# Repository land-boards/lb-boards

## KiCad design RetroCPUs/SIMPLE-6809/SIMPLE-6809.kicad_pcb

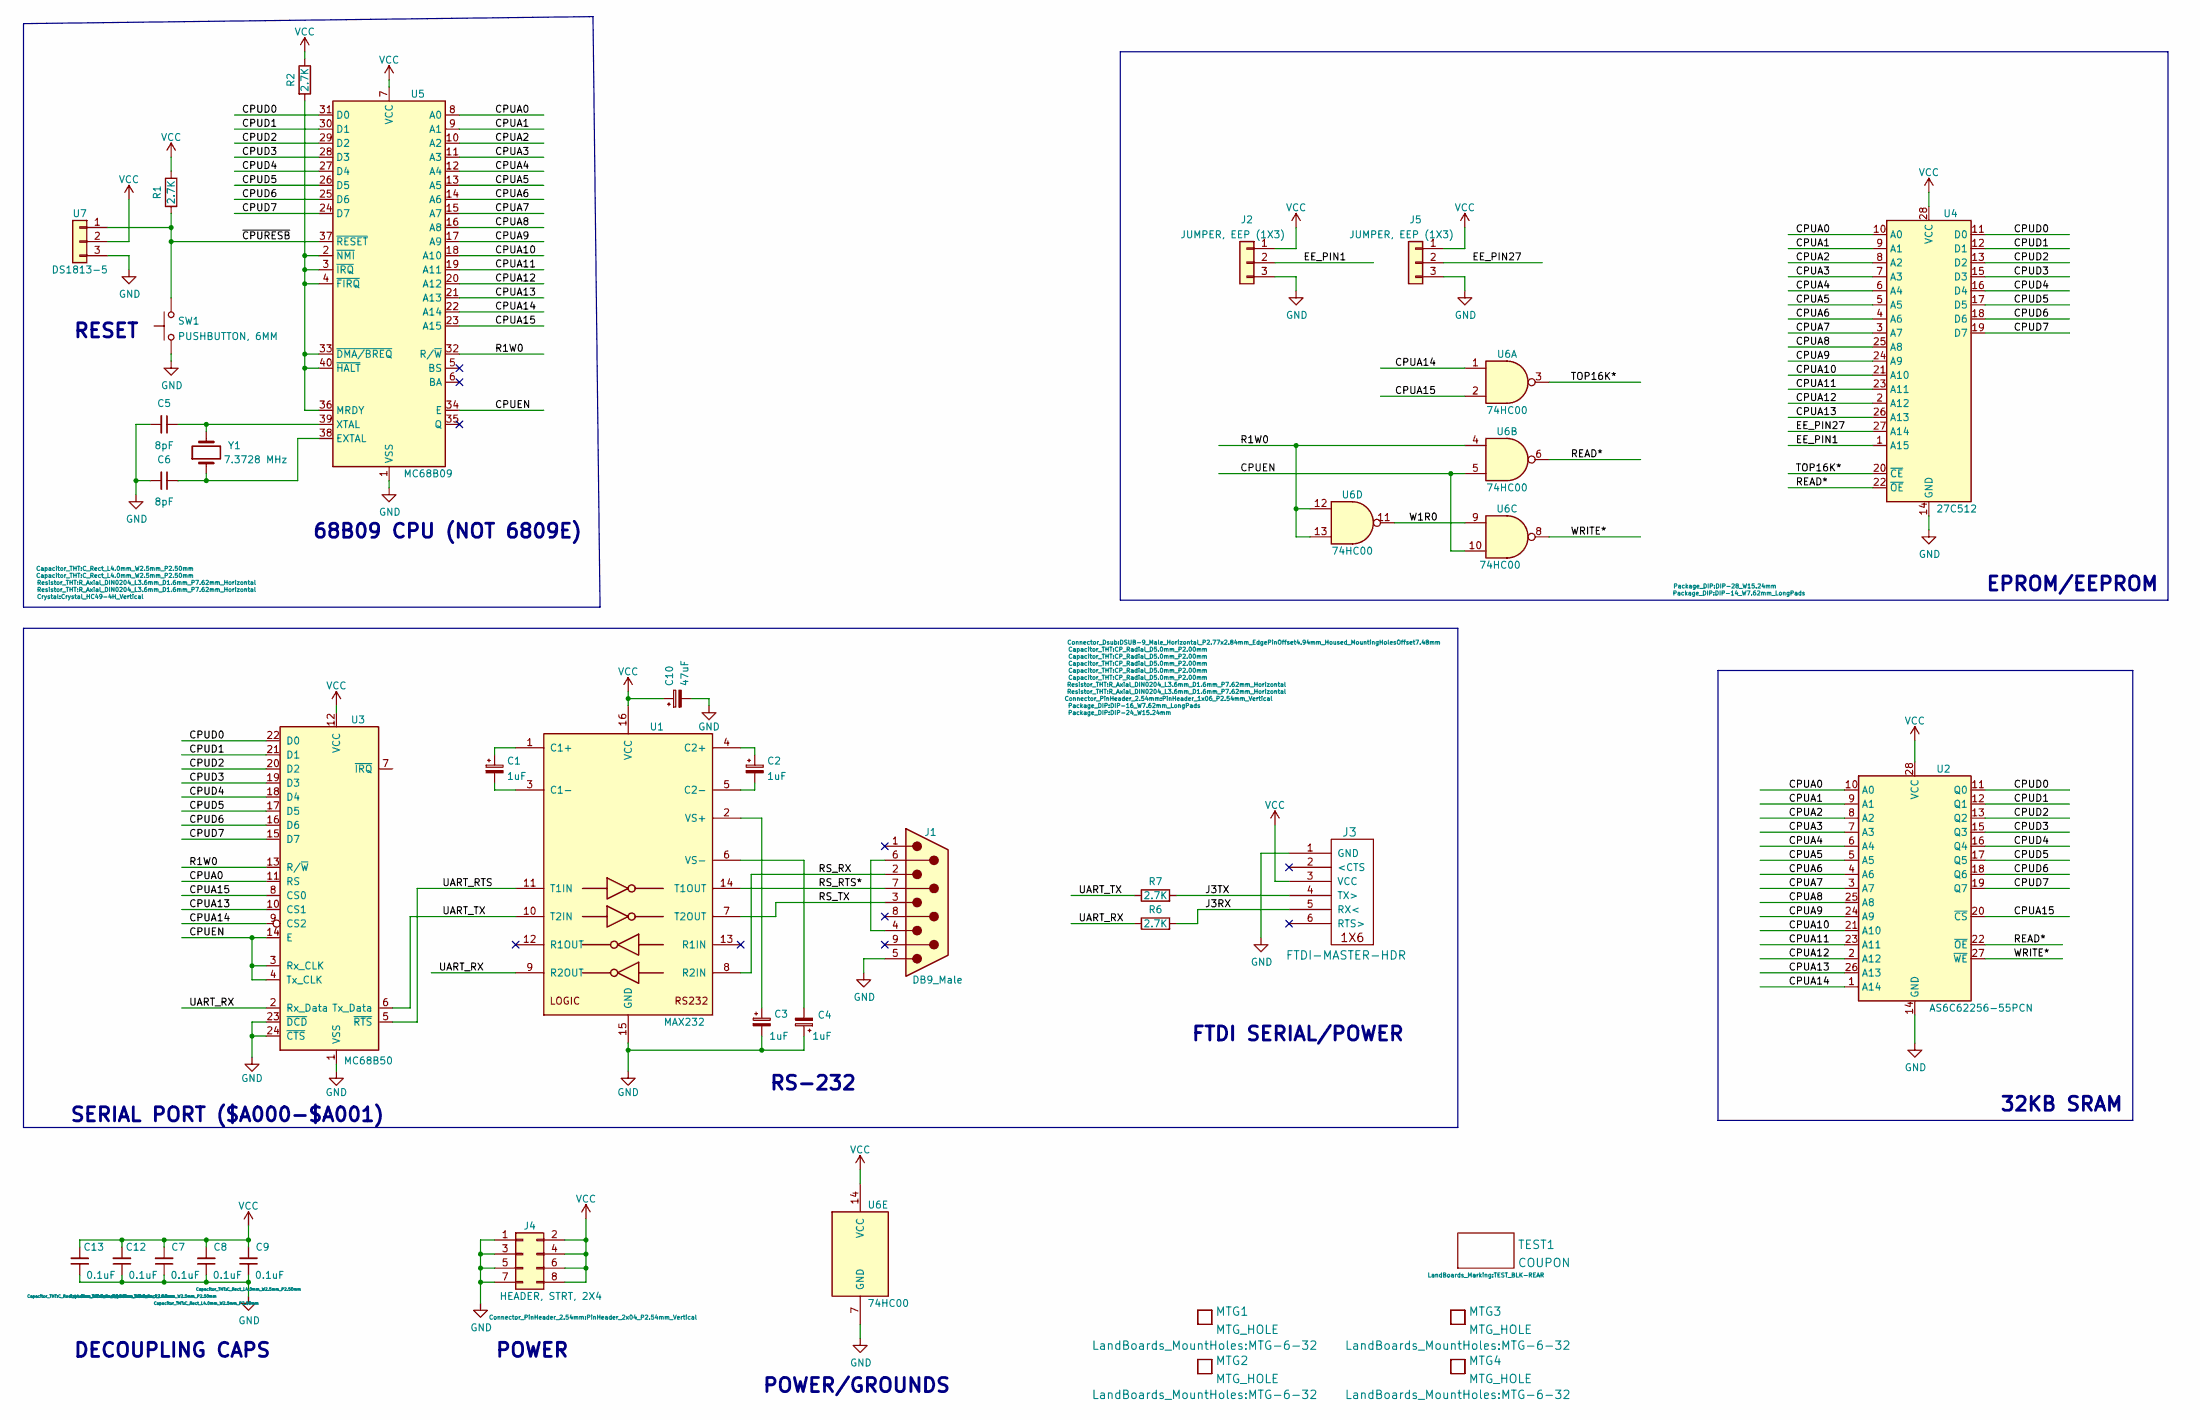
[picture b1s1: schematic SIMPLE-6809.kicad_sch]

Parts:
C1, C2, C3, C4: 1uF; CP_Radial_D5.0mm_P2.00mm
C5, C6: 8pF; C_Rect_L4.0mm_W2.5mm_P2.50mm
C7, C8, C9, C12, C13: 0.1uF; C_Rect_L4.0mm_W2.5mm_P2.50mm
C10: 47uF; CP_Radial_D5.0mm_P2.00mm
J1: DB9_Male; DSUB-9_Male_Horizontal_P2.77x2.84mm_EdgePinOffset4.94mm_Hou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
J2, J5: JUMPER, EEP (1X3); PinHeader_1x03_P2.54mm_Vertical
J3: FTDI-MASTER-HDR; PinHeader_1x06_P2.54mm_Vertical
J4: HEADER, STRT, 2X4; PinHeader_2x04_P2.54mm_Vertical
MTG1, MTG2, MTG3, MTG4: MTG_HOLE; MTG-6-32
R1, R2, R6, R7: 2.7K; R_Axial_DIN0204_L3.6mm_D1.6mm_P7.62mm_Horizontal
SW1: PUSHBUTTON, 6MM; SW_PUSH_6mm_H8.5mm
TEST1: COUPON; TEST_BLK-REAR
U1: MAX232; DIP-16_W7.62mm_LongPads
U2: AS6C62256-55PCN; DIP-28_W15.24mm
U3: MC68B50; DIP-24_W15.24mm
U4: 27C512; DIP-28_W15.24mm
U5: MC68B09; DIP-40_W15.24mm
U6: 74HC00; DIP-14_W7.62mm_LongPads
U7: DS1813-5; TO-92
Y1: 7.3728 MHz; Crystal_HC49-4H_Vertical

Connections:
/CPUA0: U2.10 (A0), U3.11 (RS), U4.10 (A0), U5.8 (A0)
/CPUA1: U2.9 (A1), U4.9 (A1), U5.9 (A1)
/CPUA2: U2.8 (A2), U4.8 (A2), U5.10 (A2)
/CPUA3: U2.7 (A3), U4.7 (A3), U5.11 (A3)
/CPUA4: U2.6 (A4), U4.6 (A4), U5.12 (A4)
/CPUA5: U2.5 (A5), U4.5 (A5), U5.13 (A5)
/CPUA6: U2.4 (A6), U4.4 (A6), U5.14 (A6)
/CPUA7: U2.3 (A7), U4.3 (A7), U5.15 (A7)
/CPUA8: U2.25 (A8), U4.25 (A8), U5.16 (A8)
/CPUA9: U2.24 (A9), U4.24 (A9), U5.17 (A9)
/CPUA10: U2.21 (A10), U4.21 (A10), U5.18 (A10)
/CPUA11: U2.23 (A11), U4.23 (A11), U5.19 (A11)
/CPUA12: U2.2 (A12), U4.2 (A12), U5.20 (A12)
/CPUA13: U2.26 (A13), U3.10 (CS1), U4.26 (A13), U5.21 (A13)
/CPUA14: U2.1 (A14), U3.9 (CS2), U5.22 (A14), U6.1
/CPUA15: U2.20 (~CS), U3.8 (CS0), U5.23 (A15), U6.2
/CPUD0: U2.11 (Q0), U3.22 (D0), U4.11 (D0), U5.31 (D0)
/CPUD1: U2.12 (Q1), U3.21 (D1), U4.12 (D1), U5.30 (D1)
/CPUD2: U2.13 (Q2), U3.20 (D2), U4.13 (D2), U5.29 (D2)
/CPUD3: U2.15 (Q3), U3.19 (D3), U4.15 (D3), U5.28 (D3)
/CPUD4: U2.16 (Q4), U3.18 (D4), U4.16 (D4), U5.27 (D4)
/CPUD5: U2.17 (Q5), U3.17 (D5), U4.17 (D5), U5.26 (D5)
/CPUD6: U2.18 (Q6), U3.16 (D6), U4.18 (D6), U5.25 (D6)
/CPUD7: U2.19 (Q7), U3.15 (D7), U4.19 (D7), U5.24 (D7)
/CPUEN: U3.3 (Rx_CLK), U3.4 (Tx_CLK), U3.14 (E), U5.34 (E), U6.5, U6.10
/EE_PIN1: J2.2, U4.1 (A15)
/EE_PIN27: J5.2, U4.27 (A14)
/J3RX: J3.5 (RX<), R6.2
/J3TX: J3.4 (TX>), R7.2
/R1W0: U3.13 (R/~W), U5.32 (R/~W), U6.4, U6.12, U6.13
/READ*: U2.22 (~OE), U4.22 (~OE), U6.6
/RS_RTS*: J1.7, U1.14 (T1OUT)
/RS_RX: J1.2, U1.8 (R2IN)
/RS_TX: J1.3, U1.7 (T2OUT)
/TOP16K*: U4.20 (~CE), U6.3
/UART_RTS: U1.11 (T1IN), U3.5 (~RTS)
/UART_RX: R6.1, U1.9 (R2OUT), U3.2 (Rx_Data)
/UART_TX: R7.1, U1.10 (T2IN), U3.6 (Tx_Data)
/W1R0: U6.9, U6.11
/WRITE*: U2.27 (~WE), U6.8
/~CPURESB: R1.2, SW1.2, U5.37 (~RESET), U7.1
GND: C3.2, C4.1, C5.2, C6.2, C7.1, C8.1, C9.1, C10.2, C12.1, C13.1, J1.5, J2.3, J3.1 (GND), J4.1, J4.3, J4.5, J4.7, J5.3, SW1.1, U1.15 (GND), U2.14 (GND), U3.1 (VSS), U3.23 (~DCD), U3.24 (~CTS), U4.14 (GND), U5.1 (VSS), U6.7 (GND), U7.3
unnamed: J1.4, J1.6
unnamed: C1.1, U1.1 (C1+)
unnamed: C1.2, U1.3 (C1-)
unnamed: C2.1, U1.4 (C2+)
unnamed: C2.2, U1.5 (C2-)
unnamed: C3.1, U1.2 (VS+)
unnamed: C4.2, U1.6 (VS-)
unnamed: C6.1, U5.38 (EXTAL), Y1.1
unnamed: R2.2, U5.2 (~NMI), U5.3 (~IRQ), U5.4 (~FIRQ), U5.33 (~DMA/BREQ), U5.36 (MRDY), U5.40 (~HALT)
unnamed: C5.1, U5.39 (XTAL), Y1.2
VCC: C7.2, C8.2, C9.2, C10.1, C12.2, C13.2, J2.1, J3.3 (VCC), J4.2, J4.4, J4.6, J4.8, J5.1, R1.1, R2.1, U1.16 (VCC), U2.28 (VCC), U3.12 (VCC), U4.28 (VCC), U5.7 (VCC), U6.14 (VCC), U7.2

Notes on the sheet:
POWER
RESET
32KB SRAM
DECOUPLING CAPS
FTDI SERIAL/POWER
SERIAL PORT ($A000-$A001)
POWER/GROUNDS
EPROM/EEPROM
68B09 CPU (NOT 6809E)
RS-232

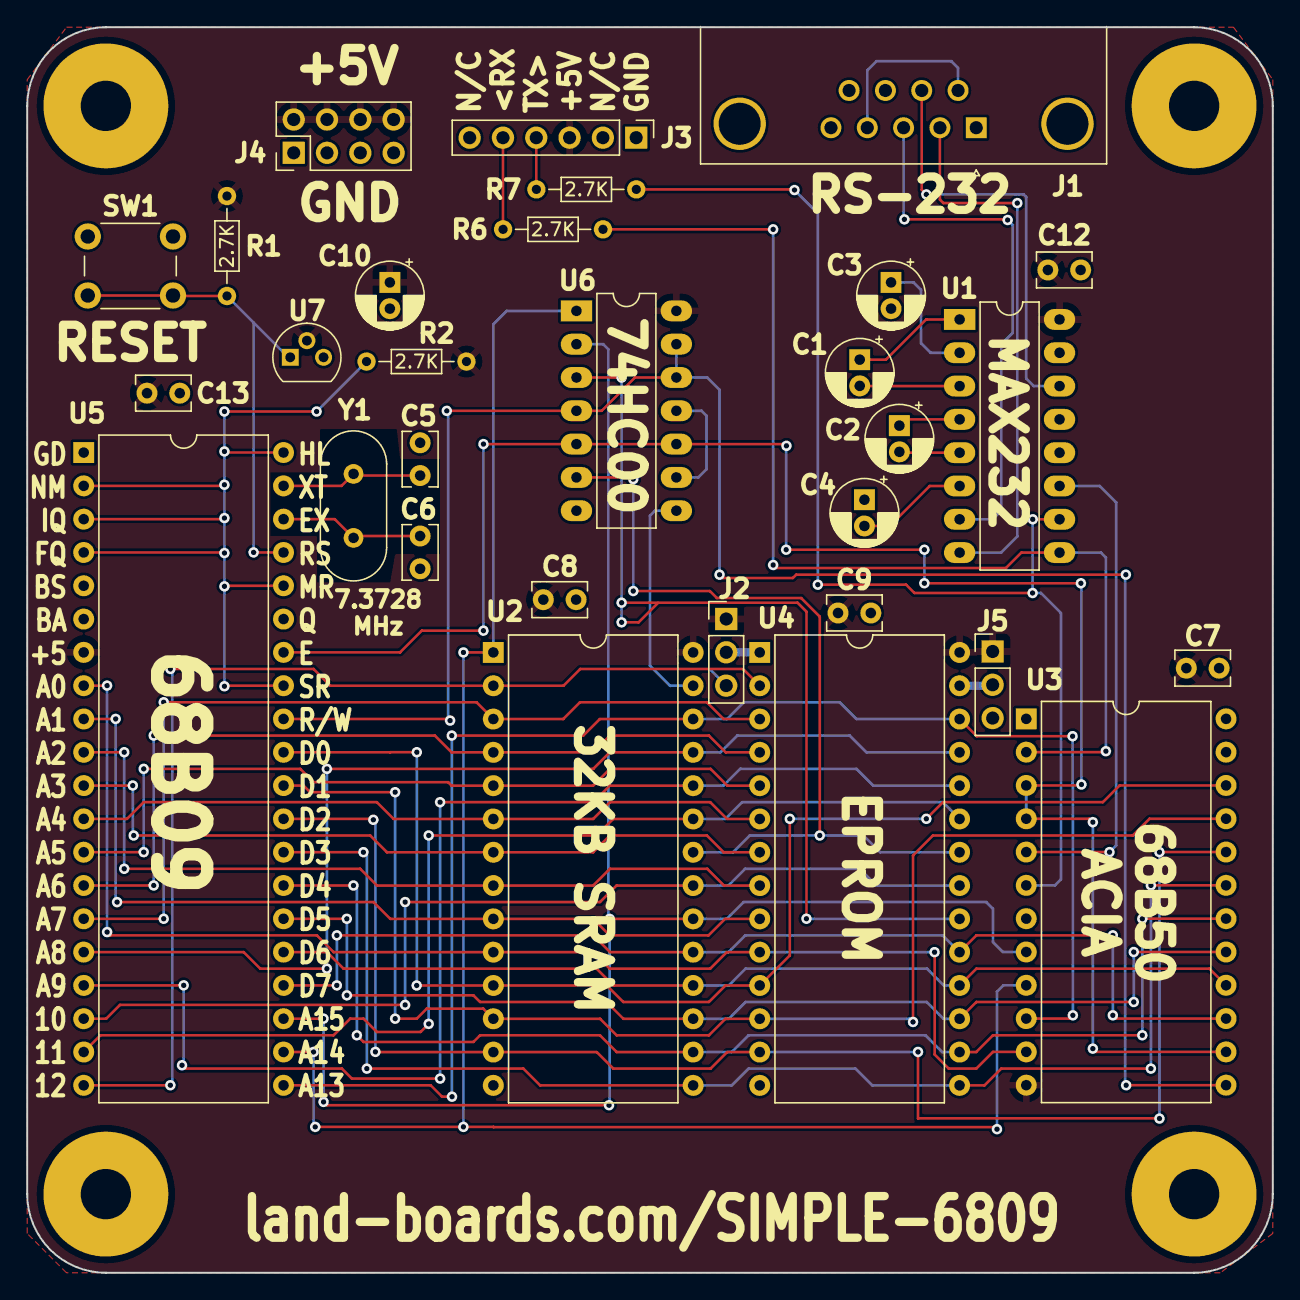
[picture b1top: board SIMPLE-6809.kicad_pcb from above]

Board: 2 copper layers, 95.0 x 95.0 mm, 35 parts (0 on the bottom side), 53 nets.

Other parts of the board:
TEST: COUPON; TEST_BLK-REAR

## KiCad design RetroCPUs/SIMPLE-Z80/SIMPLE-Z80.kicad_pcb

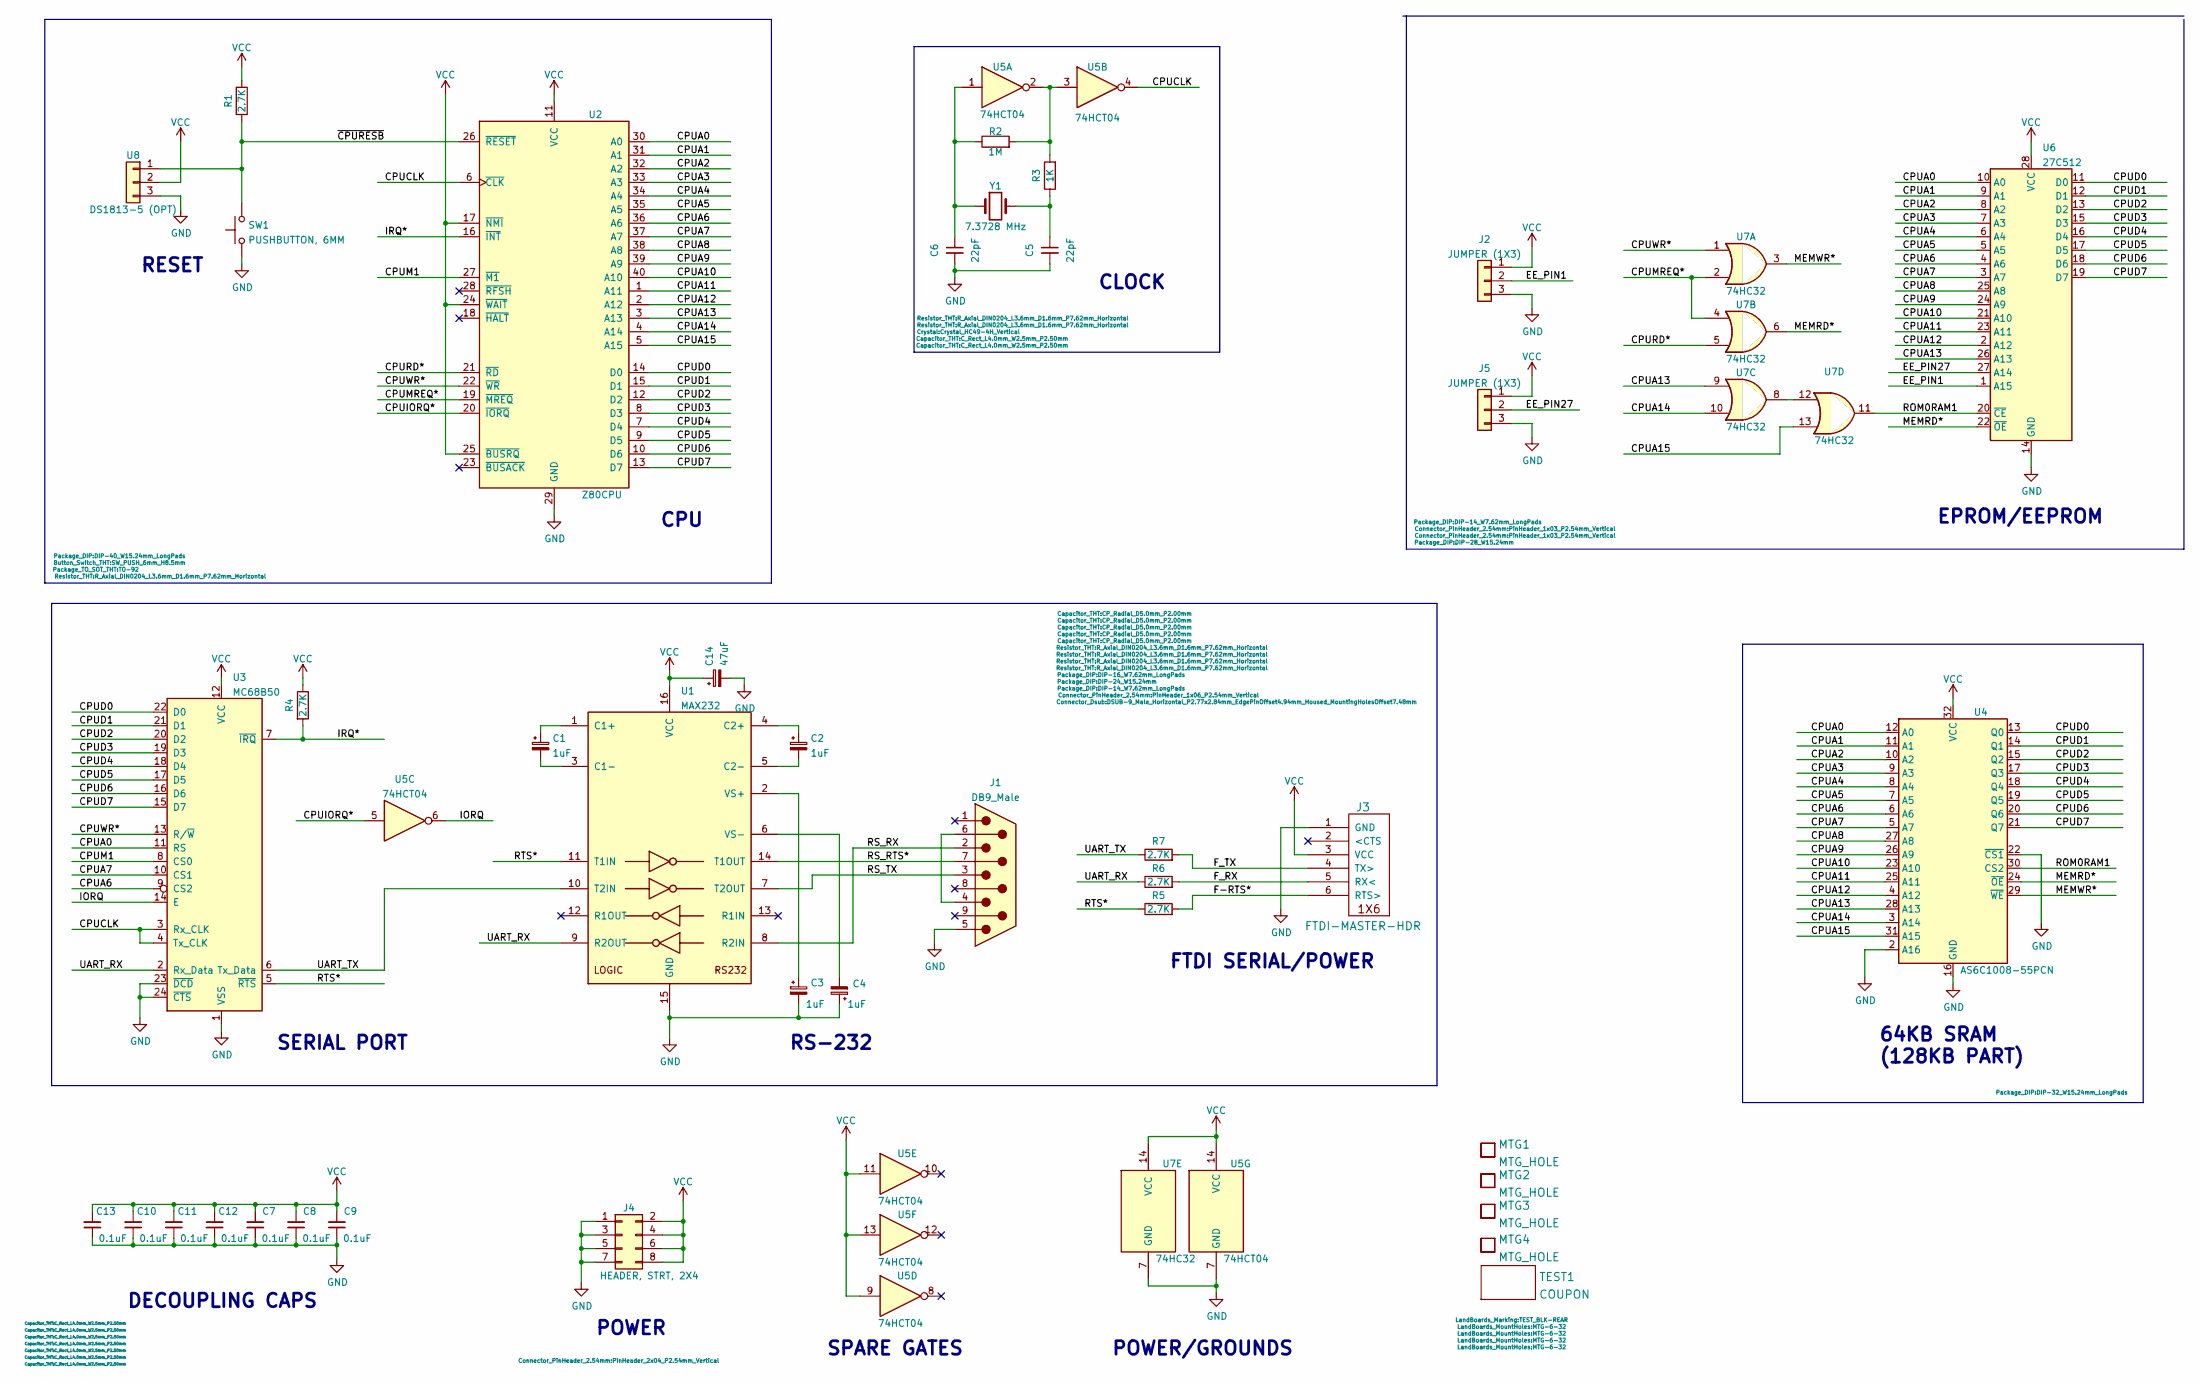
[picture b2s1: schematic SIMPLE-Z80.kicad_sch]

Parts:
C1, C2, C3, C4: 1uF; CP_Radial_D5.0mm_P2.00mm
C5, C6: 22pF; C_Rect_L4.0mm_W2.5mm_P2.50mm
C7, C8, C9, C10, C11, C12, C13: 0.1uF; C_Rect_L4.0mm_W2.5mm_P2.50mm
C14: 47uF; CP_Radial_D5.0mm_P2.00mm
J1: DB9_Male; DSUB-9_Male_Horizontal_P2.77x2.84mm_EdgePinOffset4.94mm_Hou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
J2, J5: JUMPER (1X3); PinHeader_1x03_P2.54mm_Vertical
J3: FTDI-MASTER-HDR; PinHeader_1x06_P2.54mm_Vertical
J4: HEADER, STRT, 2X4; PinHeader_2x04_P2.54mm_Vertical
MTG1, MTG2, MTG3, MTG4: MTG_HOLE; MTG-6-32
R1, R4, R5, R6, R7: 2.7K; R_Axial_DIN0204_L3.6mm_D1.6mm_P7.62mm_Horizontal
R2: 1M; R_Axial_DIN0204_L3.6mm_D1.6mm_P7.62mm_Horizontal
R3: 1K; R_Axial_DIN0204_L3.6mm_D1.6mm_P7.62mm_Horizontal
SW1: PUSHBUTTON, 6MM; SW_PUSH_6mm_H8.5mm
TEST1: COUPON; TEST_BLK-REAR
U1: MAX232; DIP-16_W7.62mm_LongPads
U2: Z80CPU; DIP-40_W15.24mm_LongPads
U3: MC68B50; DIP-24_W15.24mm
U4: AS6C1008-55PCN; DIP-32_W15.24mm_LongPads
U5: 74HCT04; DIP-14_W7.62mm_LongPads
U6: 27C512; DIP-28_W15.24mm
U7: 74HC32; DIP-14_W7.62mm_LongPads
U8: DS1813-5 (OPT); TO-92
Y1: 7.3728 MHz; Crystal_HC49-4H_Vertical

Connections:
/CPUA0: U2.30 (A0), U3.11 (RS), U4.12 (A0), U6.10 (A0)
/CPUA1: U2.31 (A1), U4.11 (A1), U6.9 (A1)
/CPUA2: U2.32 (A2), U4.10 (A2), U6.8 (A2)
/CPUA3: U2.33 (A3), U4.9 (A3), U6.7 (A3)
/CPUA4: U2.34 (A4), U4.8 (A4), U6.6 (A4)
/CPUA5: U2.35 (A5), U4.7 (A5), U6.5 (A5)
/CPUA6: U2.36 (A6), U3.9 (CS2), U4.6 (A6), U6.4 (A6)
/CPUA7: U2.37 (A7), U3.10 (CS1), U4.5 (A7), U6.3 (A7)
/CPUA8: U2.38 (A8), U4.27 (A8), U6.25 (A8)
/CPUA9: U2.39 (A9), U4.26 (A9), U6.24 (A9)
/CPUA10: U2.40 (A10), U4.23 (A10), U6.21 (A10)
/CPUA11: U2.1 (A11), U4.25 (A11), U6.23 (A11)
/CPUA12: U2.2 (A12), U4.4 (A12), U6.2 (A12)
/CPUA13: U2.3 (A13), U4.28 (A13), U6.26 (A13), U7.9
/CPUA14: U2.4 (A14), U4.3 (A14), U7.10
/CPUA15: U2.5 (A15), U4.31 (A15), U7.13
/CPUCLK: U2.6 (~CLK), U3.3 (Rx_CLK), U3.4 (Tx_CLK), U5.4
/CPUD0: U2.14 (D0), U3.22 (D0), U4.13 (Q0), U6.11 (D0)
/CPUD1: U2.15 (D1), U3.21 (D1), U4.14 (Q1), U6.12 (D1)
/CPUD2: U2.12 (D2), U3.20 (D2), U4.15 (Q2), U6.13 (D2)
/CPUD3: U2.8 (D3), U3.19 (D3), U4.17 (Q3), U6.15 (D3)
/CPUD4: U2.7 (D4), U3.18 (D4), U4.18 (Q4), U6.16 (D4)
/CPUD5: U2.9 (D5), U3.17 (D5), U4.19 (Q5), U6.17 (D5)
/CPUD6: U2.10 (D6), U3.16 (D6), U4.20 (Q6), U6.18 (D6)
/CPUD7: U2.13 (D7), U3.15 (D7), U4.21 (Q7), U6.19 (D7)
/CPUIORQ*: U2.20 (~IORQ), U5.5
/CPUM1: U2.27 (~M1), U3.8 (CS0)
/CPUMREQ*: U2.19 (~MREQ), U7.2, U7.4
/CPURD*: U2.21 (~RD), U7.5
/CPUWR*: U2.22 (~WR), U3.13 (R/~W), U7.1
/EE_PIN1: J2.2, U6.1 (A15)
/EE_PIN27: J5.2, U6.27 (A14)
/F-RTS*: J3.6 (CTS>), R5.2
/F_RX: J3.5 (TX<), R6.2
/F_TX: J3.4 (RX>), R7.2
/IORQ: U3.14 (E), U5.6
/IRQ*: R4.2, U2.16 (~INT), U3.7 (~IRQ)
/MEMRD*: U4.24 (~OE), U6.22 (~OE), U7.6
/MEMWR*: U4.29 (~WE), U7.3
/ROM0RAM1: U4.30 (CS2), U6.20 (~CE), U7.11
/RS_RTS*: J1.7, U1.14 (T1OUT)
/RS_RX: J1.2, U1.8 (R2IN)
/RS_TX: J1.3, U1.7 (T2OUT)
/RTS*: R5.1, U1.11 (T1IN), U3.5 (~RTS)
/UART_RX: R6.1, U1.9 (R2OUT), U3.2 (Rx_Data)
/UART_TX: R7.1, U1.10 (T2IN), U3.6 (Tx_Data)
/~CPURESB: R1.2, SW1.2, U2.26 (~RESET), U8.1
GND: C3.2, C4.1, C5.2, C6.2, C7.1, C8.1, C9.1, C10.1, C11.1, C12.1, C13.1, C14.2, J1.5, J2.3, J3.1 (GND), J4.1, J4.3, J4.5, J4.7, J5.3, SW1.1, U1.15 (GND), U2.29 (GND), U3.1 (VSS), U3.23 (~DCD), U3.24 (~CTS), U4.2 (A16), U4.16 (GND), U4.22 (~CS1), U5.7 (GND), U6.14 (GND), U7.7 (GND), U8.3
unnamed: C5.1, R3.1, Y1.2
unnamed: C6.1, R2.1, U5.1, Y1.1
unnamed: J1.4, J1.6
unnamed: R2.2, R3.2, U5.2, U5.3
unnamed: C1.1, U1.1 (C1+)
unnamed: C1.2, U1.3 (C1-)
unnamed: C2.1, U1.4 (C2+)
unnamed: C2.2, U1.5 (C2-)
unnamed: C3.1, U1.2 (VS+)
unnamed: C4.2, U1.6 (VS-)
unnamed: U7.8, U7.12
VCC: C7.2, C8.2, C9.2, C10.2, C11.2, C12.2, C13.2, C14.1, J2.1, J3.3 (VCC), J4.2, J4.4, J4.6, J4.8, J5.1, R1.1, R4.1, U1.16 (VCC), U2.11 (VCC), U2.17 (~NMI), U2.24 (~WAIT), U2.25 (~BUSRQ), U3.12 (VCC), U4.32 (VCC), U5.9, U5.11, U5.13, U5.14 (VCC), U6.28 (VCC), U7.14 (VCC), U8.2

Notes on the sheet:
POWER
RESET
64KB SRAM (128KB PART)
DECOUPLING CAPS
SPARE GATES
FTDI SERIAL/POWER
SERIAL PORT
POWER/GROUNDS
EPROM/EEPROM
CPU
CLOCK
RS-232

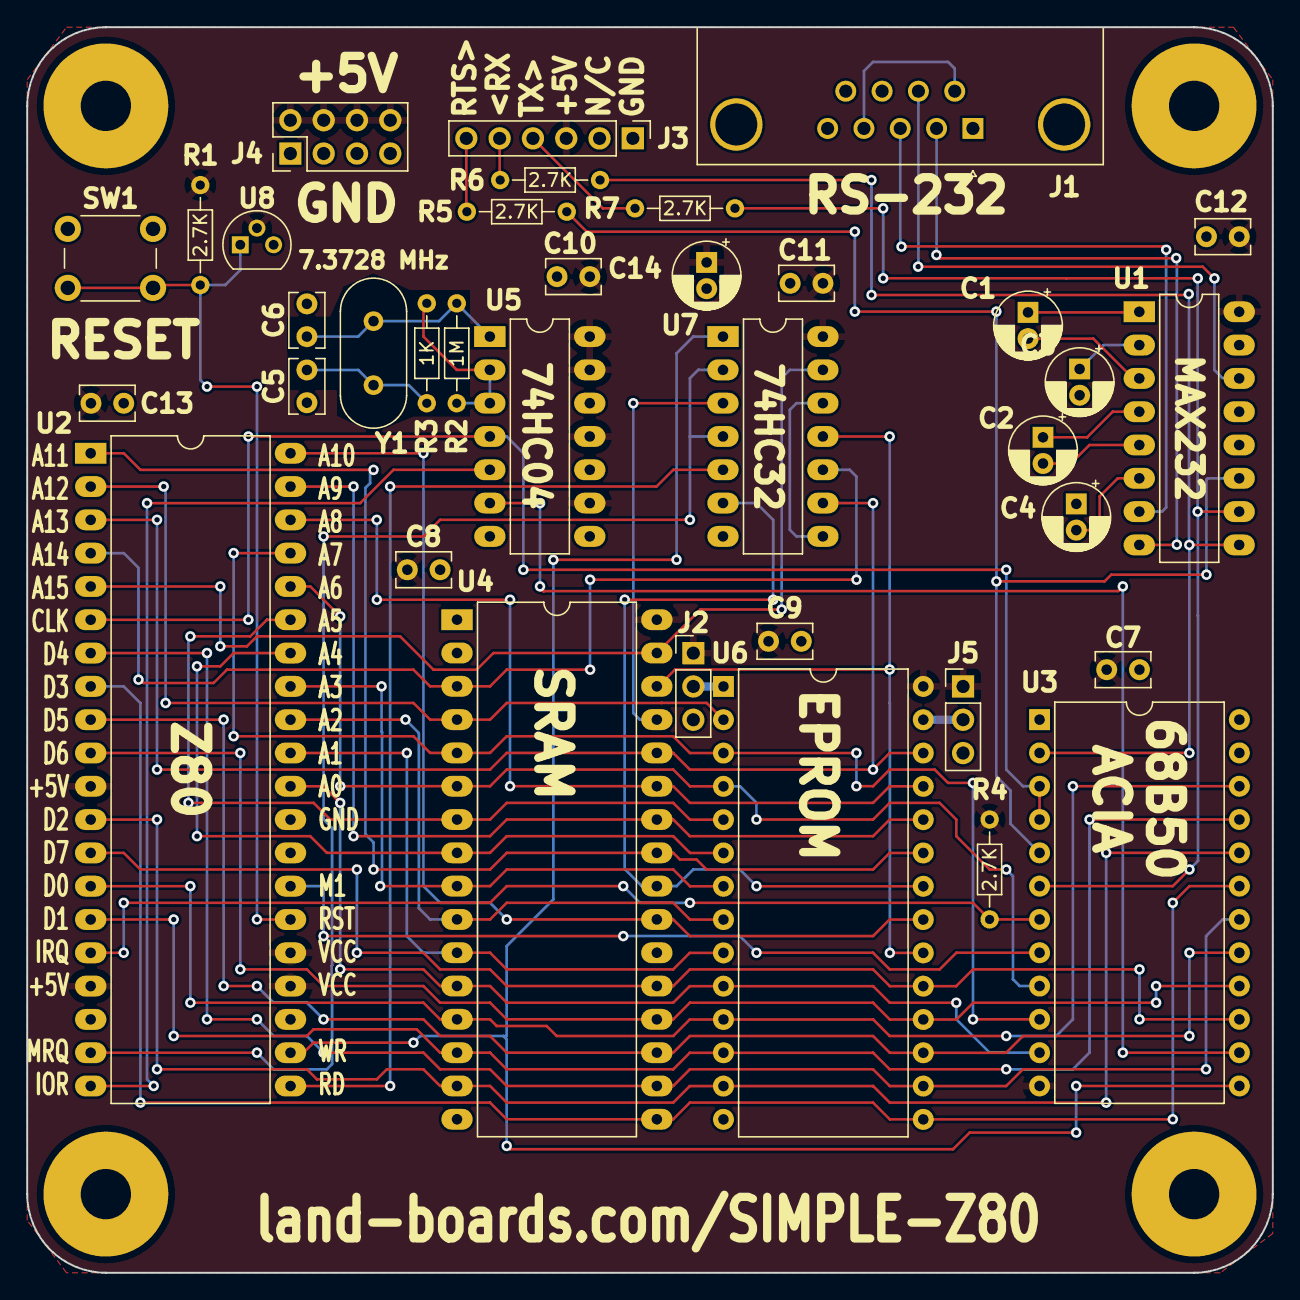
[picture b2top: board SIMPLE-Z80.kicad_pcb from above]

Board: 2 copper layers, 95.0 x 95.0 mm, 41 parts (0 on the bottom side), 60 nets.

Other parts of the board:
TEST: COUPON; TEST_BLK-REAR

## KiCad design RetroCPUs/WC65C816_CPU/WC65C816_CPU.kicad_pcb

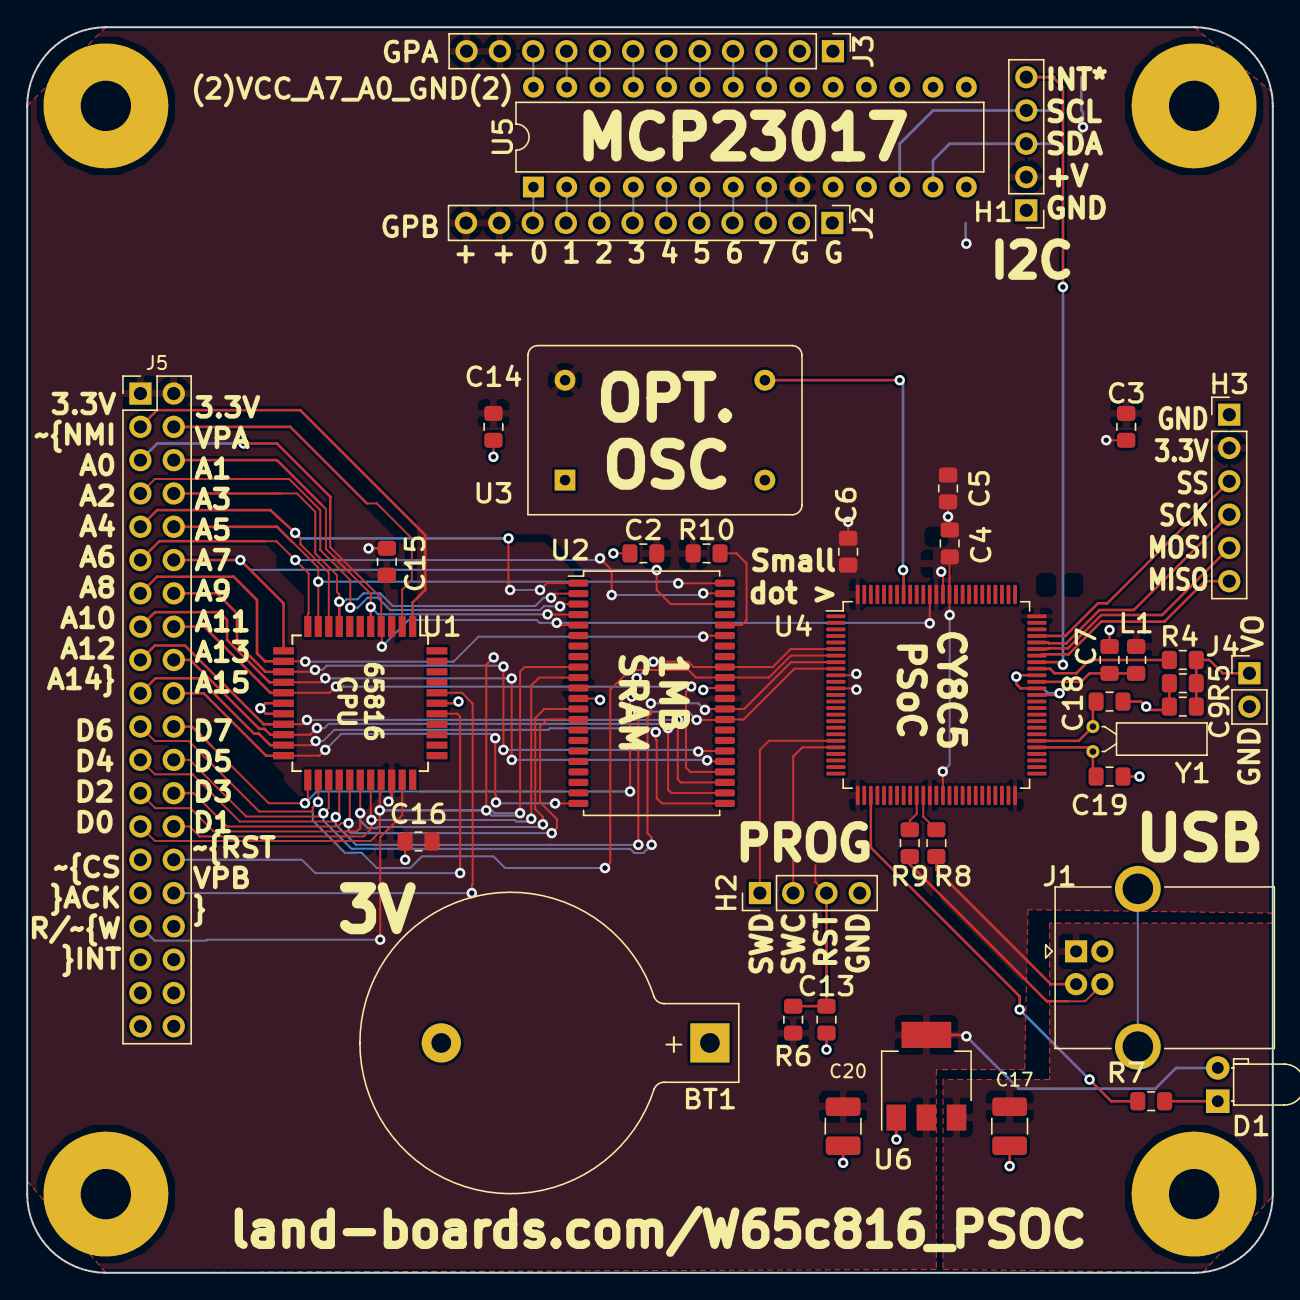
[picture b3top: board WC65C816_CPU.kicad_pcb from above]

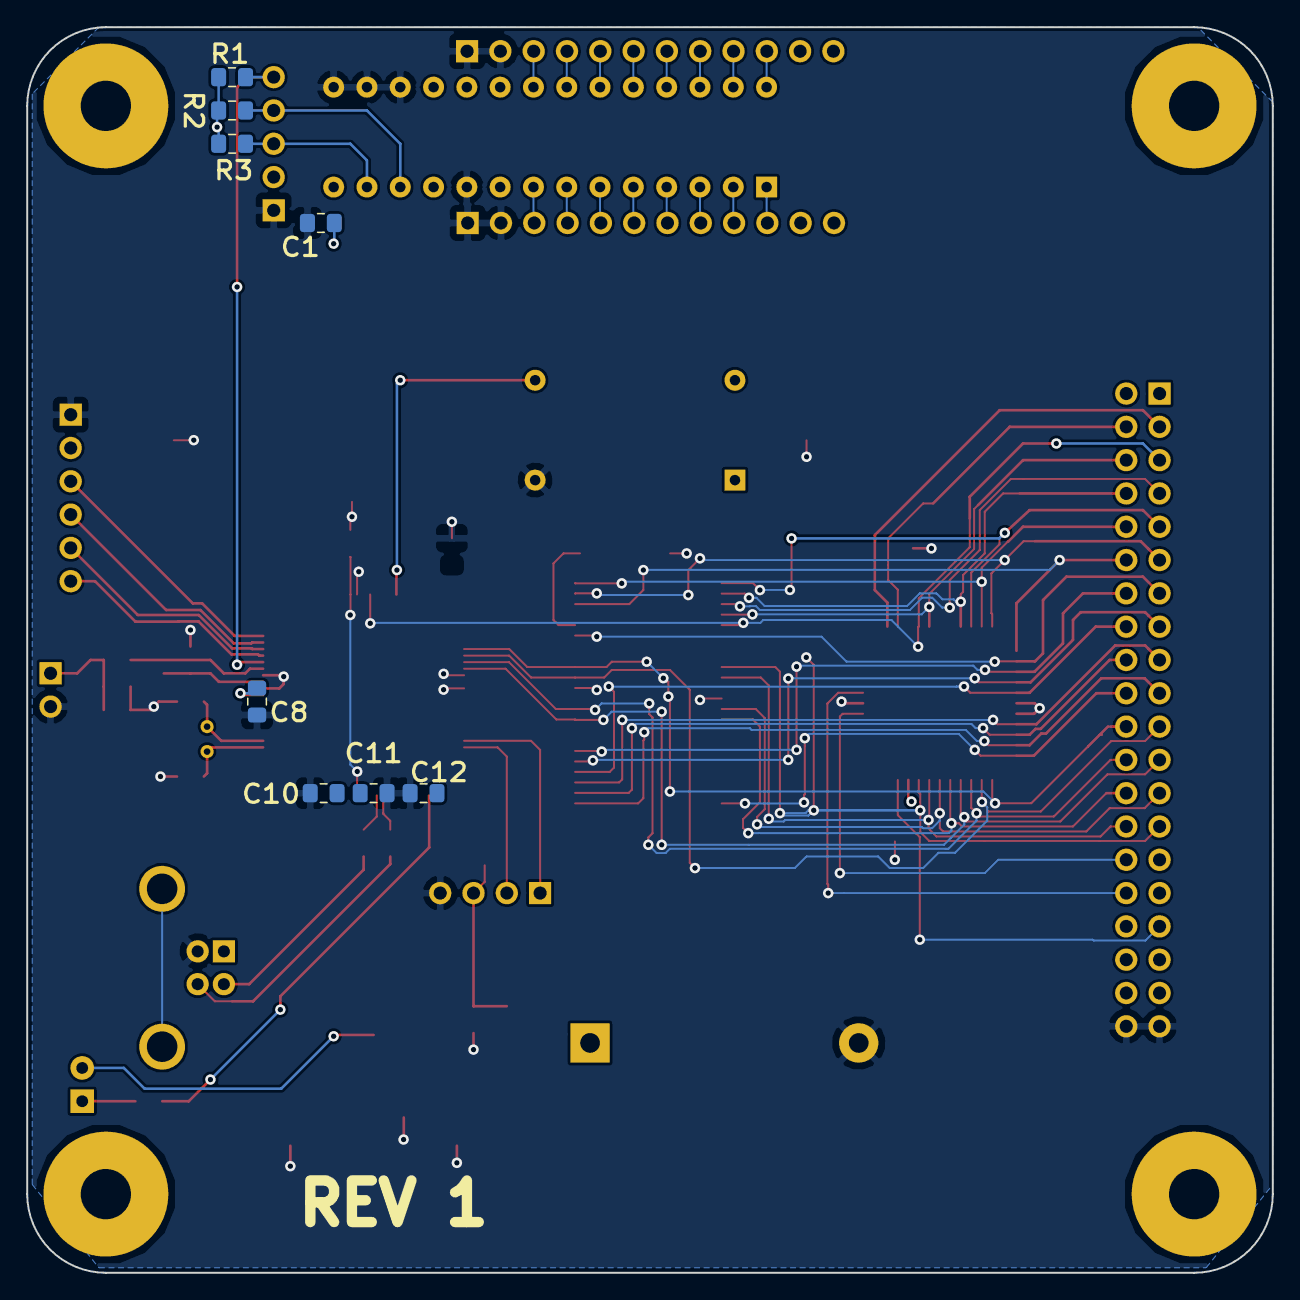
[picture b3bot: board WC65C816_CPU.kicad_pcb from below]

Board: 2 copper layers, 95.0 x 95.0 mm, 52 parts (8 on the bottom side), 91 nets.

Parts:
BT1: Battery_Cell; BatteryHolder_Keystone_103_1x20mm
C1, C2, C3, C5, C6, C11, C12, C13, C14, C15, C16: 0.1uF; C_0805_2012Metric_Pad1.15x1.40mm_HandSolder
C4, C7, C8, C10: 1uF; C_0805_2012Metric_Pad1.15x1.40mm_HandSolder
C9: 0.001uF; C_0805_2012Metric_Pad1.15x1.40mm_HandSolder
C17, C20: 10uF; C_1210_3225Metric_Pad1.42x2.65mm_HandSolder
C18, C19: 8pF; C_0805_2012Metric_Pad1.15x1.40mm_HandSolder
D1: LED; LED_D3.0mm_Horizontal_O1.27mm_Z2.0mm
H1: Conn_01x05; PinHeader_1x05_P2.54mm_Vertical
H2: Conn_01x04; PinHeader_1x04_P2.54mm_Vertical
H3: Conn_01x06; PinHeader_1x06_P2.54mm_Vertical
J1: USB_B; USB_B_OST_USB-B1HSxx_Horizontal
J2, J3: Conn_01x12; PinHeader_1x12_P2.54mm_Vertical
J4: Conn_01x02; PinHeader_1x02_P2.54mm_Vertical
J5: Conn_02x20_Odd_Even; PinHeader_2x20_P2.54mm_Vertical
L1: ChipInd; L_0805_2012Metric_Pad1.15x1.40mm_HandSolder
MTG1, MTG2, MTG3, MTG4: MTG_HOLE; MTG-6-32
R1, R2, R3, R4, R10: 2.2K; R_0805_2012Metric_Pad1.15x1.40mm_HandSolder
R5: 100; R_0805_2012Metric_Pad1.15x1.40mm_HandSolder
R6: 3.9K; R_0805_2012Metric_Pad1.15x1.40mm_HandSolder
R7: 330; R_0805_2012Metric_Pad1.15x1.40mm_HandSolder
R8, R9: 22; R_0805_2012Metric_Pad1.15x1.40mm_HandSolder
U1: W65C816S; LQFP-44_10x10mm_P0.8mm
U2: IS62WV10248EBLL-45TLI; TSOP-II-44_10.16x18.41mm_P0.8mm
U3: 4.9152 MHz; Oscillator_DIP-14
U4: CY8C5267AXI-LP051; TQFP-100_14x14mm_P0.5mm
U5: MCP23017_SP; DIP-28_W7.62mm
U6: AP1117; SOT-223
Y1: 32.768KHz; Crystal_C26-LF_D2.1mm_L6.5mm_Horizontal

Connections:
+3V3: C1.2, C2.2, C3.2, C5.2, C6.2, C11.2, C12.2, C14.2, C15.2, C16.2, C20.2, D1.2, H1.2, H3.2, J2.11, J2.12, J3.11, J3.12, J5.1, J5.2, L1.2, R1.1, R2.1, R3.1, R6.1, R10.2, U1.3, U1.31, U2.11, U2.33, U3.14, U4.26, U4.37, U4.50, U4.75, U4.88, U4.100, U5.9, U6.2, U6.4
+5V: C17.2, J1.1, U6.3
/BE: U1.34, U4.43
/CPUA0: J5.5, U1.4, U2.5, U4.89
/CPUA1: J5.6, U1.5, U2.4, U4.90
/CPUA2: J5.7, U1.7, U2.3, U4.91
/CPUA3: J5.8, U1.8, U2.2, U4.92
/CPUA4: J5.9, U1.9, U2.1, U4.95
/CPUA5: J5.10, U1.10, U2.44, U4.96
/CPUA6: J5.11, U1.11, U2.43, U4.97
/CPUA7: J5.12, U1.12, U2.42, U4.98
/CPUA8: J5.13, U1.13, U2.39, U4.2
/CPUA9: J5.14, U1.14, U2.28, U4.22
/CPUA10: J5.15, U1.15, U2.27, U4.19
/CPUA11: J5.16, U1.16, U2.26, U4.81
/CPUA12: J5.17, U1.19, U2.25, U4.31
/CPUA13: J5.18, U1.20, U2.24, U4.32
/CPUA14: J5.19, U1.21, U2.23, U4.33
/CPUA15: J5.20, U1.22, U2.22, U4.34
/CPUD0: J5.27, U1.30, U2.9
/CPUD1: J5.28, U1.29, U2.10, U4.16
/CPUD2: J5.25, U1.28, U2.13, U4.17
/CPUD3: J5.26, U1.27, U2.14, U4.18
/CPUD4: J5.23, U1.26, U2.31, U4.9
/CPUD5: J5.24, U1.25, U2.32, U4.8
/CPUD6: J5.21, U1.24, U2.35, U4.7
/CPUD7: J5.22, U1.23, U2.36, U4.6
/DAC_OUT: R4.2, U4.67
/E: U1.33, U4.52
/GPA0: J3.3, U5.21
/GPA1: J3.4, U5.22
/GPA2: J3.5, U5.23
/GPA3: J3.6, U5.24
/GPA4: J3.7, U5.25
/GPA5: J3.8, U5.26
/GPA6: J3.9, U5.27
/GPA7: J3.10, U5.28
/GPB0: J2.10, U5.1
/GPB1: J2.9, U5.2
/GPB2: J2.8, U5.3
/GPB3: J2.7, U5.4
/GPB4: J2.6, U5.5
/GPB5: J2.5, U5.6
/GPB6: J2.4, U5.7
/GPB7: J2.3, U5.8
/LED: R7.2, U4.28
/MX: U1.36, U4.51
/R/~W: J5.33, U1.32, U4.42
/RCS: R10.1, U2.40
/RDY: U1.41, U4.83
/SCL: H1.4, R2.2, U4.4, U5.12
/SDA: H1.3, R3.2, U4.5, U5.13
/SPIMISO: H3.6, U4.69
/SPIMOSI: H3.5, U4.70
/SPISCK: H3.4, U4.71
/SPISS: H3.3, U4.72
/SRAMA16: U2.21, U4.47
/SRAMA17: U2.20, U4.46
/SRAMA18: U2.19, U4.45
/SRAMA19: U2.18, U4.44
/SWC: H2.2, U4.21
/SWD: H2.1, U4.20
/USB-DM: J1.2, R8.1
/USB-DP: J1.3, R9.1
/VDA: U1.37, U4.49
/VPA: J5.4, U1.2, U4.79
/VPB: J5.32, U1.40, U4.24
/~ABTB: U1.42, U4.84
/~I2CINT: H1.5, R1.2, U4.68
/~IOACK: J5.31, U4.25
/~IOCS: J5.29, U4.27
/~IOINT: J5.35, U4.53
/~IRQ: U1.43, U4.85
/~MEMWR: U2.17, U4.73
/~ML: U1.44, U4.82
/~NMI: J5.3, U1.1, U4.78
/~RESB: J5.30, U1.38, U4.23, U5.18
/~SRAMCS: U2.6, U4.74
GND: BT1.2, C1.1, C2.1, C3.1, C4.2, C5.1, C6.1, C7.2, C8.2, C9.1, C10.2, C11.1, C12.1, C13.2, C14.1, C15.1, C16.1, C17.1, C18.1, C19.1, C20.1, H1.1, H2.4, H3.1, J1.4, J2.1, J2.2, J3.1, J3.2, J4.2, J5.39, J5.40, R5.1, U1.17, U1.18, U1.39, U2.12, U2.34, U3.7, U4.10, U4.12, U4.14, U4.38, U4.64, U4.66, U4.87, U5.10, U5.15, U5.16, U5.17, U6.1
unnamed: BT1.1, U4.13
unnamed: C7.1, L1.1, U4.65
unnamed: C8.1, U4.63
unnamed: C9.2, J4.1, R4.1, R5.2
unnamed: C4.1, C10.1, U4.39, U4.86
unnamed: C13.1, H2.3, R6.2, U4.15
unnamed: C18.2, U4.56, Y1.2
unnamed: C19.2, U4.55, Y1.1
unnamed: D1.1, R7.1
unnamed: R8.2, U4.36
unnamed: R9.2, U4.35
unnamed: U3.8, U4.93

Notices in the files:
SYNTHS/Docs/Modules/Mutable Instruments/MI Branches/STIX/STIX.kicad_pcb:
cc-by-sa-3.0 2013
